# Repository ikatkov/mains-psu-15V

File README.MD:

The simplest possible mains PSU
I needed one for the used Tektronix active probe (p6201) I bought off ebay.

The PSU take 120V mains and outputs +/- 15V, 175mA max (each rail)
I added varistor, 250mA fuse on the input and 15V zeners on the output.

If one tries to draw more current, the mains ripple appears on the output.

See LTSpice folder for the sim files.
See Kicad folder for schematic/pcb layout

Interesting bits:

* It is a full wave voltage dubler PSU. https://sound-au.com/project05-mini.htm
This is rather unfortunate, but the transformer I salvaged only had ~17VAC, this is not enough for the more conventional type with a full wave bridge rectifier. The price is much larger input caps and extra heat that is burned when voltage is regulated down to +/- 15V.

* Two LEDs are here to signal that both rails are healthy and bleed off these large resistors. If a regulator shutdowns (over current, overheating) corresponding LED goes off.

* Large, 2W 3 Ohm resistors are there to burn heat, and reduce the heat dissipation requirments for the voltage regulator. I did not have smaller, 2W rated, ones. If I did - the PSU could either use smaller caps, or product larger output current.

* Since this is not a switching PSU, not extra filtering is needed. Not backfeed filtering is needed either.

* I use aluminum enclosure as a heat sink. Regulators are connected by wires to the PCB and screwed right to the aluminum.

* For the enclosure - I saw a large salvaged box one in halfs, 3d printed a PETG cap where IEC AC socket and AC main switch are mounted.

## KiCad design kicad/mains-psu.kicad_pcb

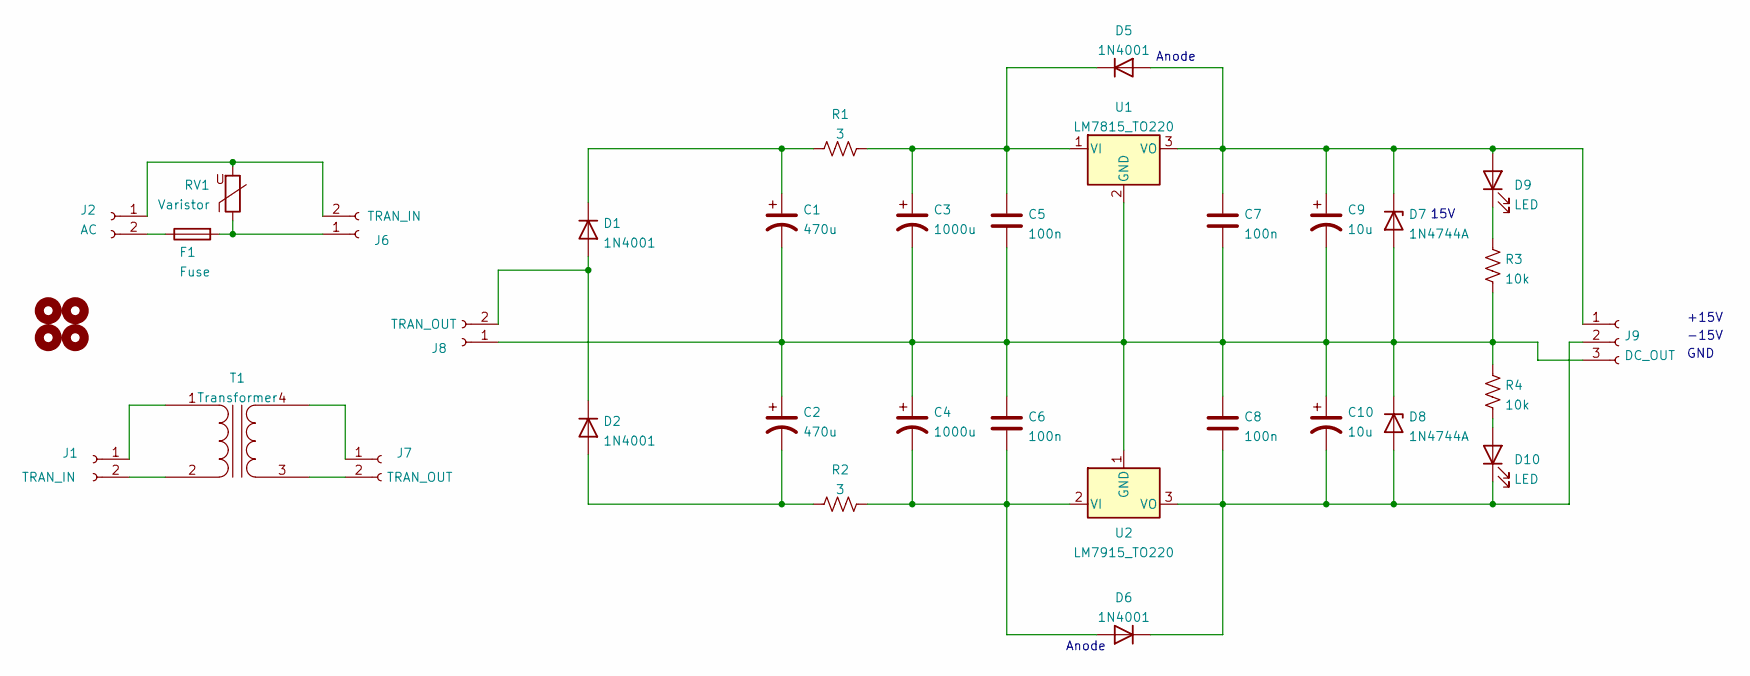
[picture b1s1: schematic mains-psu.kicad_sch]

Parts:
C1, C2: 470u; CP_Radial_D13.0mm_P7.50mm
C3, C4: 1000u; CP_Radial_D13.0mm_P7.50mm
C5, C6, C7, C8: 100n; C_Disc_D5.0mm_W2.5mm_P5.00mm
C9, C10: 10u; CP_Radial_D5.0mm_P2.50mm
D1, D2: 1N4001; D_DO-41_SOD81_P10.16mm_Horizontal
D5, D6: 1N4001; D_DO-41_SOD81_P5.08mm_Vertical_AnodeUp
D7, D8: 1N4744A; D_DO-41_SOD81_P5.08mm_Vertical_AnodeUp
D9, D10: LED; LED_D5.0mm
F1: Fuse; Fuseholder_Littelfuse_100_series_5x20mm
H1, H2, H3, H4: MountingHole; MountingHole_3mm
J1: TRAN_IN
J2: AC; TerminalBlock_Phoenix_MKDS-1,5-2-5.08_1x02_P5.08mm_Horizont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
J6: TRAN_IN; TerminalBlock_Phoenix_MKDS-1,5-2-5.08_1x02_P5.08mm_Horizont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
J7: TRAN_OUT
J8: TRAN_OUT; TerminalBlock_Phoenix_MKDS-1,5-2-5.08_1x02_P5.08mm_Horizont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
J9: DC_OUT; JST_XH_B3B-XH-A_1x03_P2.50mm_Vertical
R1, R2: 3; R_Axial_Power_L20.0mm_W6.4mm_P22.40mm
R3, R4: 10k; R_Axial_DIN0207_L6.3mm_D2.5mm_P7.62mm_Horizontal
RV1: Varistor; RV_Disc_D12mm_W5mm_P7.5mm
T1: Transformer
U1: LM7815_TO220; TO-220F-3_Horizontal_TabDown
U2: LM7915_TO220; TO-220F-3_Horizontal_TabDown

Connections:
unnamed: C1.1, D1.1 (K), R1.1
unnamed: C1.2, C2.1, C3.2, C4.1, C5.2, C6.1, C7.2, C8.1, C9.2, C10.1, D7.2 (A), D8.1 (K), J8.1, J9.3, R3.1, R4.2, U1.2 (GND), U2.1 (GND)
unnamed: C2.2, D2.2 (A), R2.1
unnamed: C3.1, C5.1, D5.1 (K), R1.2, U1.1 (VI)
unnamed: C4.2, C6.2, D6.2 (A), R2.2, U2.2 (VI)
unnamed: C7.1, C9.1, D5.2 (A), D7.1 (K), D9.2 (A), J9.1, U1.3 (VO)
unnamed: C8.2, C10.2, D6.1 (K), D8.2 (A), D10.1 (K), J9.2, U2.3 (VO)
unnamed: D1.2 (A), D2.1 (K), J8.2
unnamed: D9.1 (K), R3.2
unnamed: D10.2 (A), R4.1
unnamed: F1.1, J2.2
unnamed: F1.2, J6.1, RV1.1
unnamed: J1.1, T1.1 (AA)
unnamed: J1.2, T1.2 (AB)
unnamed: J2.1, J6.2, RV1.2
unnamed: J7.1, T1.4 (SB)
unnamed: J7.2, T1.3 (SA)

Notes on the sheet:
+15V
Anode
GND
-15V
15V

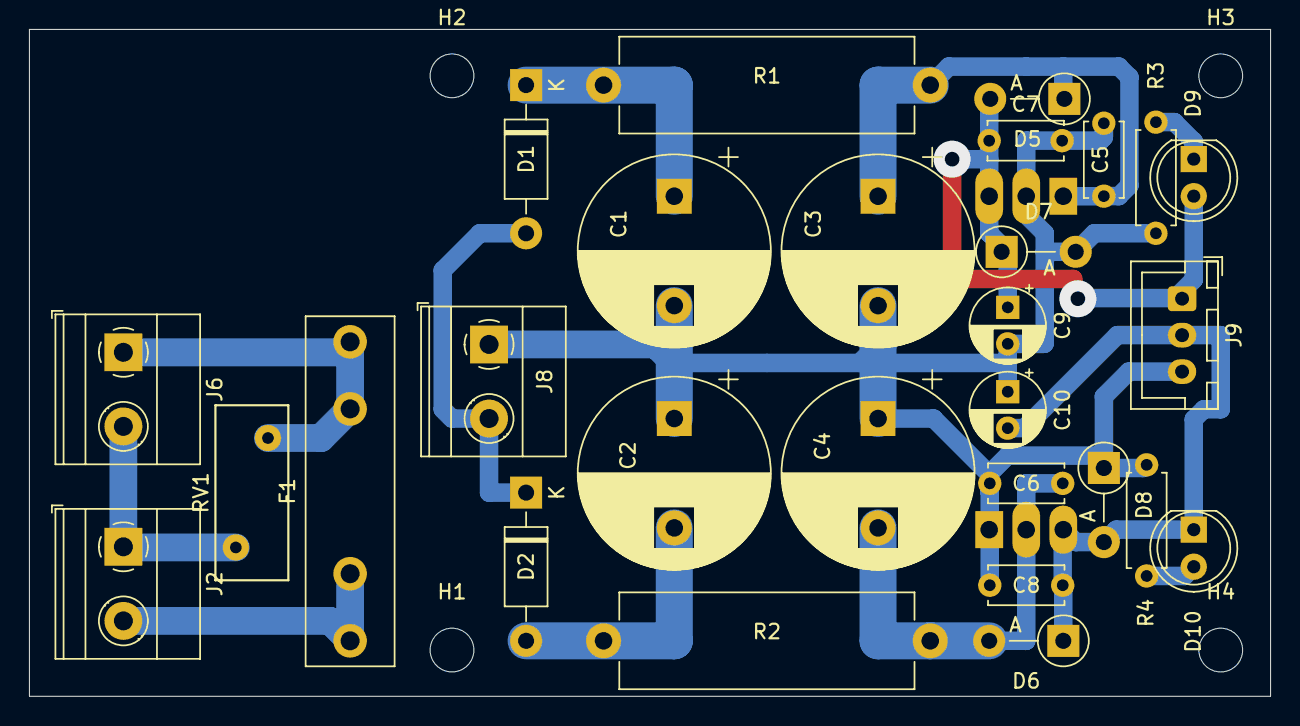
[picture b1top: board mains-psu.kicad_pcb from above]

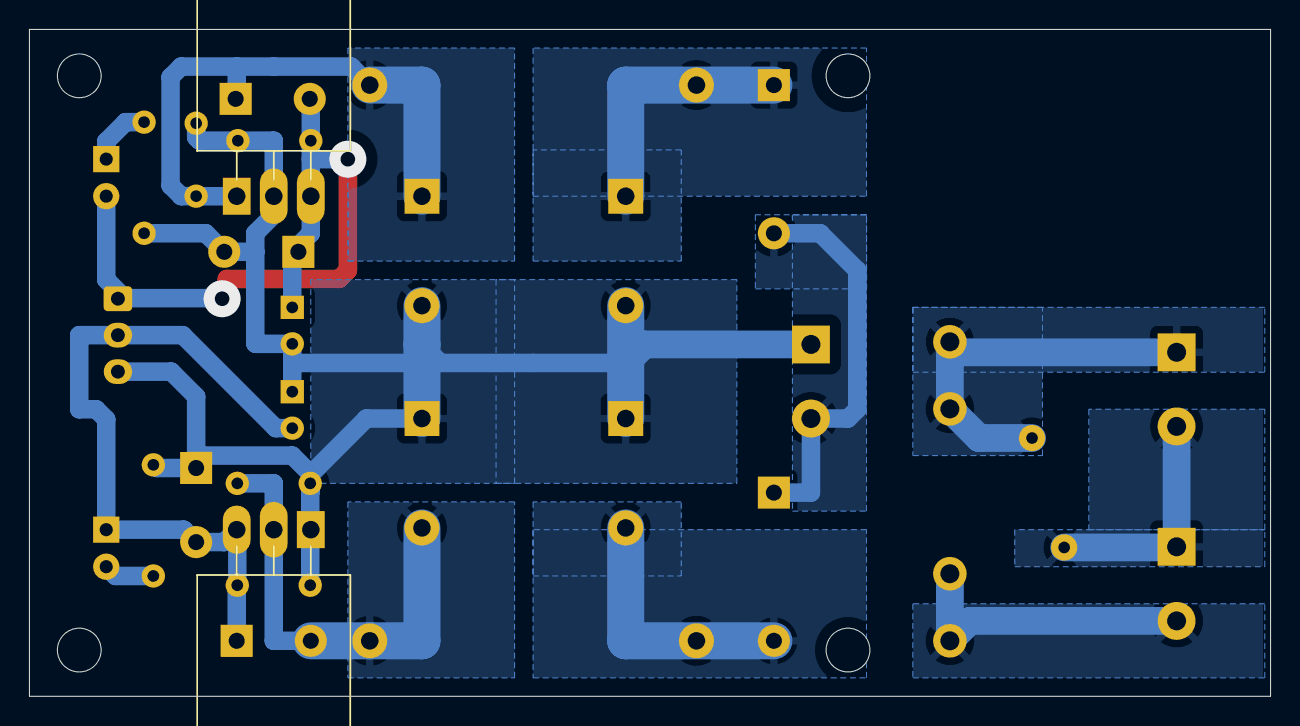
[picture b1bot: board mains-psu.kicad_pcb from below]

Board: 4 copper layers, 85.1 x 45.7 mm, 34 parts (2 on the bottom side), 13 nets.
